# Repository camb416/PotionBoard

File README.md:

# PotionBoard
Potion macropad with Adafruit Trinket Pro 5v 16Mhz

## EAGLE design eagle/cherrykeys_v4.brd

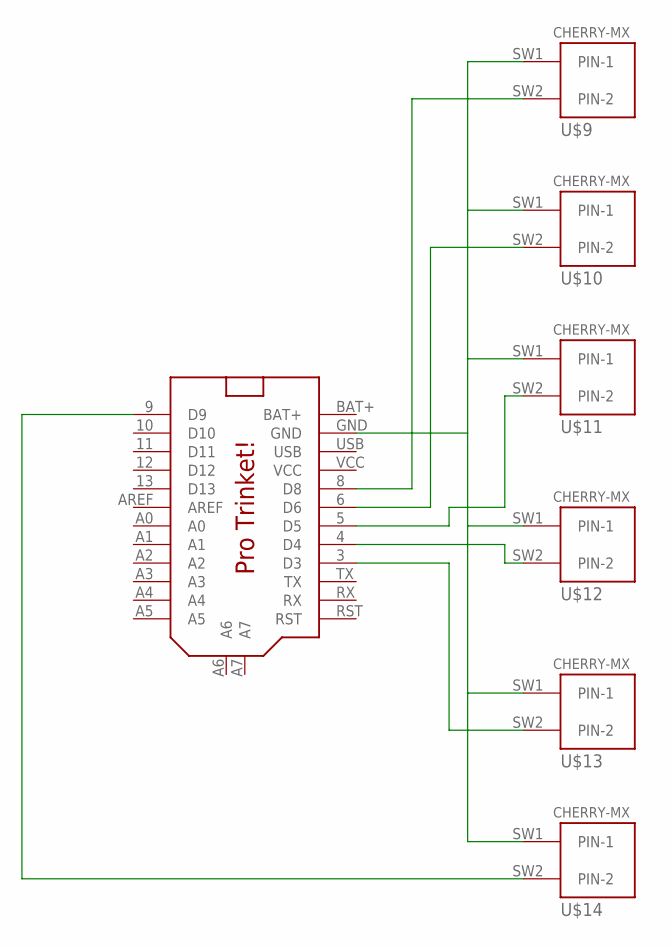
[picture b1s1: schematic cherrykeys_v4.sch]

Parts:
U$7: PRO_TRINKET; PROTRINKET
U$9, U$10, U$11, U$12, U$13, U$14: CHERRY-MX

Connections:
BAT+: U$7.BAT+
GND: U$7.GND, U$9.SW1 (PIN-1), U$10.SW1 (PIN-1), U$11.SW1 (PIN-1), U$12.SW1 (PIN-1), U$13.SW1 (PIN-1), U$14.SW1 (PIN-1)
unnamed: U$7.3 (D3), U$13.SW2 (PIN-2)
unnamed: U$7.4 (D4), U$12.SW2 (PIN-2)
unnamed: U$7.5 (D5), U$11.SW2 (PIN-2)
unnamed: U$7.6 (D6), U$10.SW2 (PIN-2)
unnamed: U$7.8 (D8), U$9.SW2 (PIN-2)
unnamed: U$7.9 (D9), U$14.SW2 (PIN-2)
USB: U$7.USB
VCC: U$7.VCC

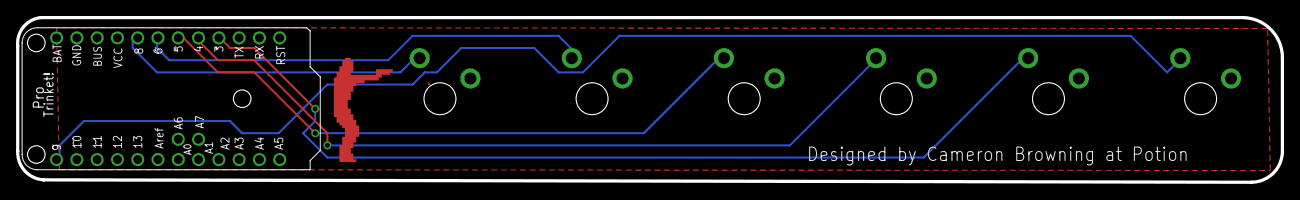
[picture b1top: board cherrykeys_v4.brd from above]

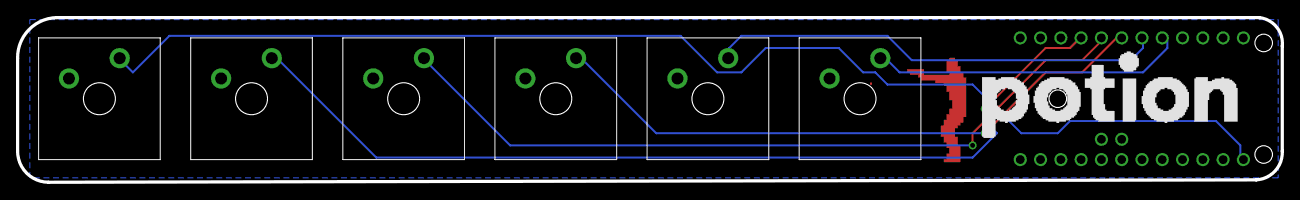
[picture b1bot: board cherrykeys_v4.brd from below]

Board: 2 copper layers, 158.4 x 20.6 mm, 7 parts (6 on the bottom side), 7 nets.

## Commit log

2017-06-21 Initial Arduino commit
2017-06-21 added photo
2017-06-22 added eagle files and screencaps
2017-06-22 less cornball more useful.
